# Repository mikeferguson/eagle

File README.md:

## Eagle CAD Stuff

This is a collection of libraries and board designs using Eagle CAD.

## Installing Eagle 7.1 (on Ubuntu 18.04)

    sudo apt-get install gcc-multilib
    sudo apt-get install libxrender1:i386 libxrandr2:i386 libxcursor1:i386 libfreetype6:i386 libfontconfig1:i386 libxi6:i386 libstdc++6:i386 libjpeg62:i386 libssl1.0.0:i386

    wget http://web.cadsoft.de/ftp/eagle/program/7.1/eagle-lin-7.1.0.run
    chmod a+x eagle-lin-7.1.0.run
    ./eagle-lin-7.1.0.run /opt

## Adding Launcher on Ubuntu 18.04
Add a file called eagle.desktop to ~/.local/share/applications:

    #!/usr/bin/env xdg-open
    [Desktop Entry]
    Comment[en_US]=Eagle 7.1
    Terminal=false
    Name[en_US]=Eagle
    Exec=/opt/eagle-7.1.0/bin/eagle
    Type=Application
    Icon=/opt/eagle-7.1.0/bin/eagleicon50.png
    StartupWMClass=dont_care

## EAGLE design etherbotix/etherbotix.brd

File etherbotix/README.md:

# Etherbotix

## Notes

Notes from stuffing Rev. A:
 * DC-DC regulator is too close to Dynamixel headers (has to be installed slightly angled away)
 * X2 footprint is missing direction indicator.
 * X2 footprint should be a bit wider for hand-stuffing.
 * C39, C40 are 22pF (might still be too high)
 * Encoder capacitor values may not be right (too aggressive of a filter)

Need to source 7/16" or 11mm length, 4-40 or M3 standoff (possibly 952-1520-ND)

## Revision History

 * Rev. B - (Forthcoming)
   * Increase size of P1 indicator on X2.
   * Moved ethernet parts away from MD-03 mounting hole
   * TODO: move U3 away from AX headers
   * TODO: move J1 (ethernet jack) up a bit to avoid collision with IMU
   * TODO: update values of C39, C40
   * TODO: update values of C4, C13, C17, C18
   * TODO: move R19, R24, R25 out from under IMU
   * Move M1 encoder filter away from MD-03 mounting hole
   * Add testpads for PE0, PE1, PE4, PA8
   * Add testpads to encoders, clocks, and current sense
   * Add jumper to force bootloader
   * TODO: change away from clikmate connector
 * Rev. A - September 7, 2014
   * First release

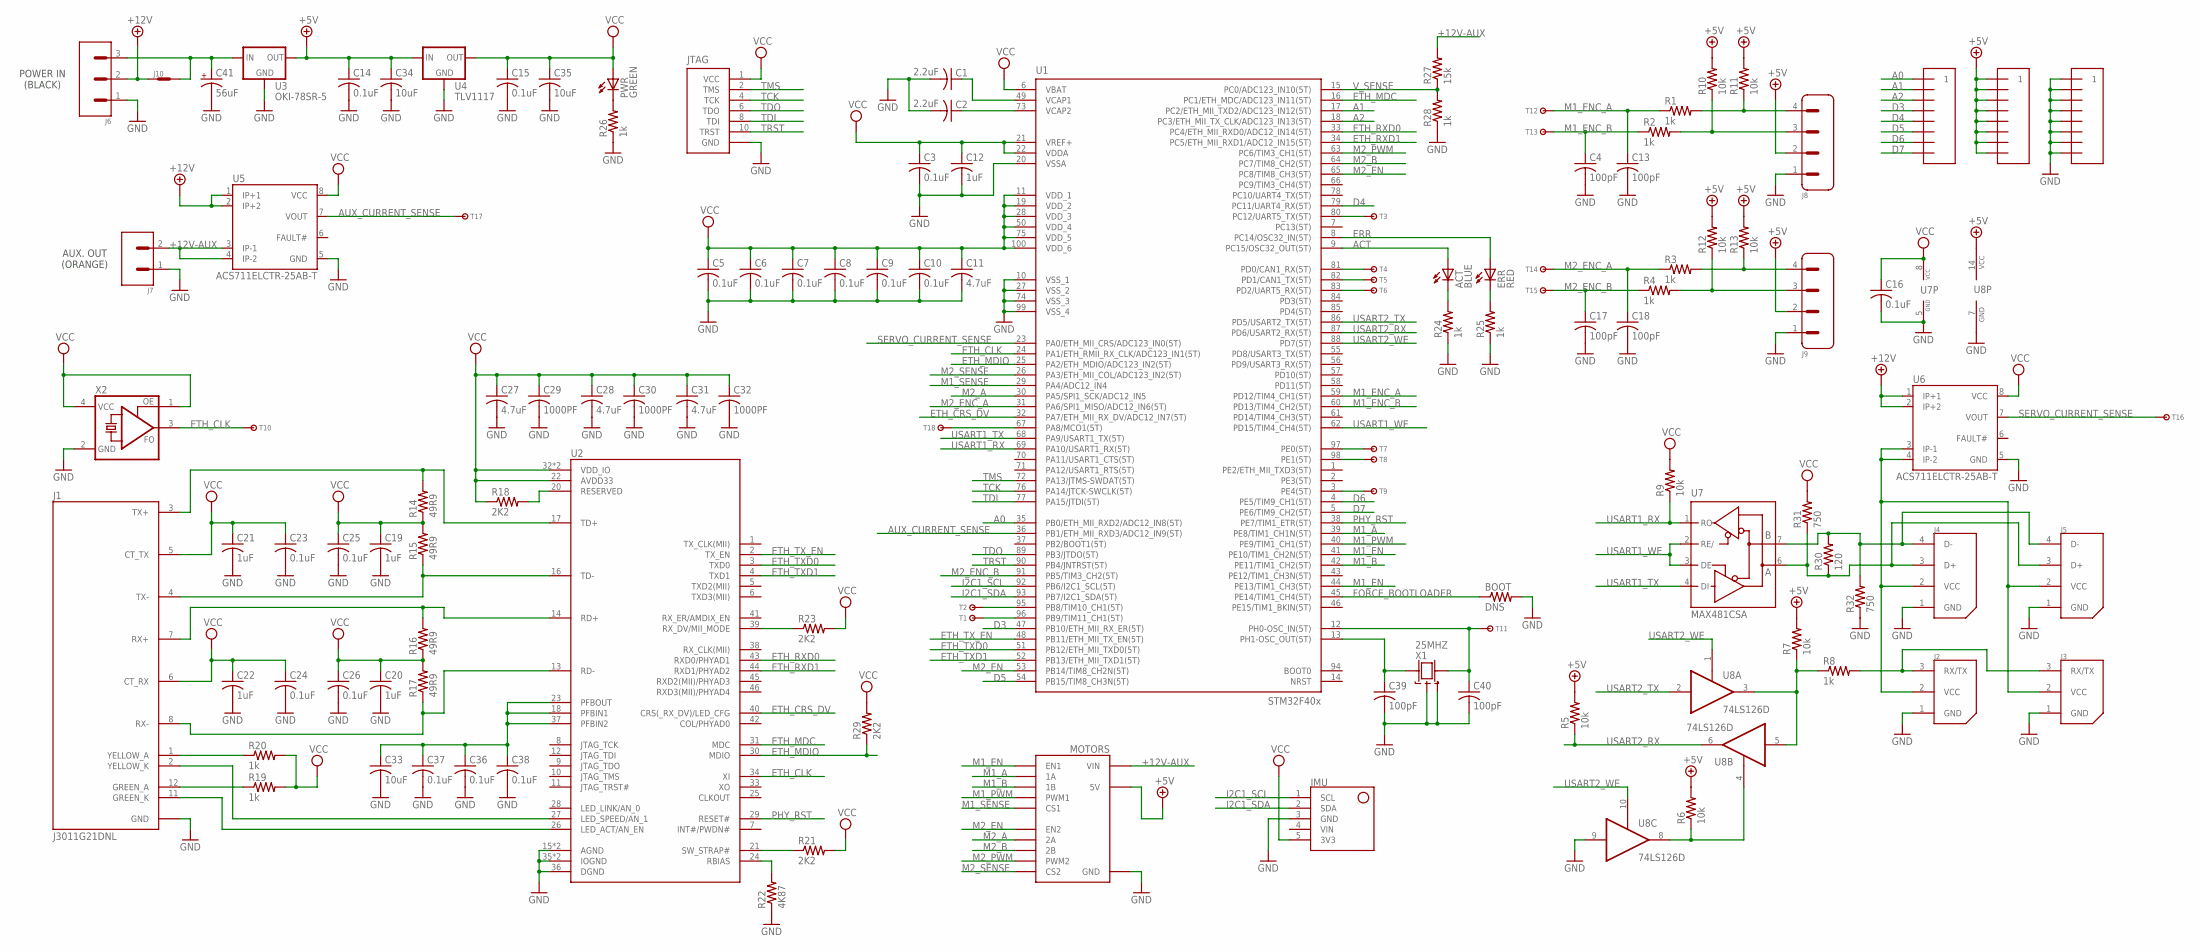
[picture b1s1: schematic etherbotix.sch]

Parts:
ACT: BLUE; LED0603
BOOT: DNS; 0603
C1, C2: 2.2uF; C0603
C3, C5, C6, C7, C8, C9, C10, C14, C15, C16, C23, C24, C25, C26, C36, C37, C38: 0.1uF; C0603
C4, C13, C17, C18, C39, C40: 100pF; C0603
C11, C27, C28, C31: 4.7uF; 0603
C12, C19, C20, C21, C22: 1uF; C0603
C29, C30, C32: 1000PF; 0603
C33, C34, C35: 10uF; C0603
C41: 56uF; OSCON_SVPF_6.3MM
ERR: RED; LED0603
IMU: MINI9IMU
J1: J3011G21DNL; J3
J2, J3: 22-03-5035; 5267-3
J4, J5: 22-03-5045; 5267-4
J6: 1760520000
J7: 1760490000
J8, J9: 502443-0470
J10: JUMPER; J2
JTAG: CORTEX_DEBUG-SHROUDED; 3220-10-0300-00
MOTORS: MD03A
PWR: GREEN; LED0603
R1, R2, R3, R4, R8, R19, R20, R24, R25, R26, R28: 1k; 0603
R5, R6, R7, R9, R10, R11, R12, R13: 10k; 0603
R14, R15, R16, R17: 49R9; 0603
R18, R21, R23, R29: 2K2; 0603
R22: 4K87; 0603
R27: 15k; 0603
R30: 120; 0603
R31, R32: 750; 0603
T1, T2, T3, T4, T5, T6, T7, T8, T9, T10, T11, T12, T13, T14, T15, T16, T17, T18: TESTPAD; TEST
U1: STM32F407V; TQFP100
U2: TLK110; LQFP48
U3: OKI-78SR-5; OKI-78SR
U4: TLV1117; DPAK
U5, U6: ACS711ELCTR-25AB-T; SOIC8
U7: MAX481CSA; SO08
U8: 74LS126D; SO14
U$1, U$2, U$3: HEADER8; 1X8
X1: 25MHZ; 4LCC
X2: ASEMB-50.000MHZ-XY-T; OSCILLATOR

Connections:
+5V: C14.1, C34.1, J8.2, J9.2, MOTORS.5V, R5.2, R6.2, R7.2, R10.2, R11.2, R12.2, R13.2, U3.P$3 (OUT), U4.3 (IN), U8.14 (VCC), U$2.P$1 (1), U$2.P$2, U$2.P$3, U$2.P$4, U$2.P$5, U$2.P$6, U$2.P$7, U$2.P$8
+12V: J6.2, J10.A, U5.1 (IP+1), U5.2 (IP+2), U6.1 (IP+1), U6.2 (IP+2)
+12V-AUX: J7.2, MOTORS.VIN1 (VIN), MOTORS.VIN2 (VIN), R27.2, U5.3 (IP-1), U5.4 (IP-2)
A0: U1.35 (PB0/ETH_MII_RXD2/ADC12_IN8(5T)), U$1.P$1 (1)
A1: U1.17 (PC2/ETH_MII_TXD2/ADC123_IN12(5T)), U$1.P$2
A2: U1.18 (PC3/ETH_MII_TX_CLK/ADC123_IN13(5T)), U$1.P$3
ACT: ACT.A, U1.9 (PC15/OSC32_OUT(5T))
AUX_CURRENT_SENSE: T17.T, U1.36 (PB1/ETH_MII_RXD3/ADC12_IN9(5T)), U5.7 (VOUT)
D3: U1.47 (PB10/ETH_MII_RX_ER(5T)), U$1.P$4
D4: U1.79 (PC11/UART4_RX(5T)), U$1.P$5
D5: U1.54 (PB15/TIM8_CH3N(5T)), U$1.P$6
D6: U1.4 (PE5/TIM9_CH1(5T)), U$1.P$7
D7: U1.5 (PE6/TIM9_CH2(5T)), U$1.P$8
ERR: ERR.A, U1.8 (PC14/OSC32_IN(5T))
ETH_CLK: T10.T, U1.24 (PA1/ETH_RMII_RX_CLK/ADC123_IN1(5T)), U2.34 (XI), X2.3 (FO)
ETH_CRS_DV: U1.32 (PA7/ETH_MII_RX_DV/ADC12_IN7(5T)), U2.40 (CRS(_RX_DV)/LED_CFG)
ETH_MDC: U1.16 (PC1/ETH_MDC/ADC123_IN11(5T)), U2.31 (MDC)
ETH_MDIO: R29.1, U1.25 (PA2/ETH_MDIO/ADC123_IN2(5T)), U2.30 (MDIO)
ETH_RXD0: U1.33 (PC4/ETH_MII_RXD0/ADC12_IN14(5T)), U2.43 (RXD0/PHYAD1)
ETH_RXD1: U1.34 (PC5/ETH_MII_RXD1/ADC12_IN15(5T)), U2.44 (RXD1/PHYAD2)
ETH_TXD0: U1.51 (PB12/ETH_MII_TXD0(5T)), U2.3 (TXD0)
ETH_TXD1: U1.52 (PB13/ETH_MII_TXD1(5T)), U2.4 (TXD1)
ETH_TX_EN: U1.48 (PB11/ETH_MII_TX_EN(5T)), U2.2 (TX_EN)
FORCE_BOOTLOADER: BOOT.1, U1.45 (PE14/TIM1_CH4(5T))
GND: BOOT.2, C1.2, C2.2, C3.2, C4.2, C5.2, C6.2, C7.2, C8.2, C9.2, C10.2, C11.2, C12.2, C13.2, C14.2, C15.2, C16.2, C17.2, C18.2, C19.2, C20.2, C21.2, C22.2, C23.2, C24.2, C25.2, C26.2, C27.2, C28.2, C29.2, C30.2, C31.2, C32.2, C33.2, C34.2, C35.2, C36.2, C37.2, C38.2, C39.2, C40.2, C41.-, IMU.3 (GND), J1.9 (GND), J1.10 (GND), J1.A (GND), J1.B (GND), J2.1 (GND), J3.1 (GND), J4.1 (GND), J5.1 (GND), J6.1, J7.1, J8.1, J9.1, JTAG.3 (GND), JTAG.5 (GND), JTAG.9 (GND), MOTORS.GND1 (GND), MOTORS.GND2 (GND), R22.1, R24.1, R25.1, R26.1, R28.1, R32.1, U1.10 (VSS_1), U1.20 (VSSA), U1.27 (VSS_2), U1.74 (VSS_3), U1.99 (VSS_4), U2.15 (AGND), U2.19 (AGND), U2.35 (IOGND), U2.36 (DGND), U2.47 (IOGND), U3.P$2 (GND), U4.1 (GND), U5.5 (GND), U6.5 (GND), U7.5 (GND), U8.7 (GND), U8.9 (I), U$3.P$1 (1), U$3.P$2, U$3.P$3, U$3.P$4, U$3.P$5, U$3.P$6, U$3.P$7, U$3.P$8, X1.2 (G1), X1.4 (G2), X2.2 (GND)
I2C1_SCL: IMU.1 (SCL), U1.92 (PB6/I2C1_SCL(5T))
I2C1_SDA: IMU.2 (SDA), U1.93 (PB7/I2C1_SDA(5T))
M1_A: MOTORS.1A, U1.39 (PE8/TIM1_CH1N(5T))
M1_B: MOTORS.1B, U1.42 (PE11/TIM1_CH2(5T))
M1_EN: MOTORS.EN1, U1.41 (PE10/TIM1_CH2N(5T)), U1.44 (PE13/TIM1_CH3(5T))
M1_ENC_A: C13.1, R1.1, T12.T, U1.59 (PD12/TIM4_CH1(5T))
M1_ENC_B: C4.1, R2.1, T13.T, U1.60 (PD13/TIM4_CH2(5T))
M1_PWM: MOTORS.PWM1, U1.40 (PE9/TIM1_CH1(5T))
M1_SENSE: MOTORS.CS1, U1.29 (PA4/ADC12_IN4)
M2_A: MOTORS.2A, U1.30 (PA5/SPI1_SCK/ADC12_IN5)
M2_B: MOTORS.2B, U1.64 (PC7/TIM8_CH2(5T))
M2_EN: MOTORS.EN2, U1.53 (PB14/TIM8_CH2N(5T)), U1.65 (PC8/TIM8_CH3(5T))
M2_ENC_A: C18.1, R3.1, T14.T, U1.31 (PA6/SPI1_MISO/ADC12_IN6(5T))
M2_ENC_B: C17.1, R4.1, T15.T, U1.91 (PB5/TIM3_CH2(5T))
M2_PWM: MOTORS.PWM2, U1.63 (PC6/TIM3_CH1(5T))
M2_SENSE: MOTORS.CS2, U1.26 (PA3/ETH_MII_COL/ADC123_IN2(5T))
unnamed: J1.4 (TX-), R15.1, U2.16 (TD-)
unnamed: J2.2 (VCC), J3.2 (VCC), J4.2 (VCC), J5.2 (VCC), U6.3 (IP-1), U6.4 (IP-2)
unnamed: C39.1, U1.13 (PH1-OSC_OUT(5T)), X1.1
unnamed: C1.1, U1.49 (VCAP1)
unnamed: C2.1, U1.73 (VCAP2)
unnamed: J8.3, R2.2, R10.1
unnamed: J8.4, R1.2, R11.1
unnamed: J9.4, R3.2, R13.1
unnamed: J9.3, R4.2, R12.1
unnamed: J4.3 (D+), J5.3 (D+), R30.1, R31.1, U7.6 (A)
unnamed: J4.4 (D-), J5.4 (D-), R30.2, R32.2, U7.7 (B)
unnamed: R7.1, R8.1, U8.3 (O), U8.5 (I)
unnamed: R6.1, U8.4 (OE), U8.8 (O)
unnamed: J2.3 (RX/TX), J3.3 (RX/TX), R8.2
unnamed: C40.1, T11.T, U1.12 (PH0-OSC_IN(5T)), X1.3
unnamed: J1.3 (TX+), R14.2, U2.17 (TD+)
unnamed: R18.2, U2.20 (RESERVED)
unnamed: J1.2 (YELLOW_K), U2.27 (LED_SPEED/AN_1)
unnamed: J1.7 (RX+), R16.2, U2.14 (RD+)
unnamed: J1.11 (GREEN_K), U2.26 (LED_ACT/AN_EN)
unnamed: J1.8 (RX-), R17.1, U2.13 (RD-)
unnamed: J1.1 (YELLOW_A), R20.1
unnamed: J1.12 (GREEN_A), R19.1
unnamed: C33.1, C36.1, C37.1, C38.1, U2.18 (PFBIN1), U2.23 (PFBOUT), U2.37 (PFBIN2)
unnamed: R21.1, U2.21 (SW_STRAP#)
unnamed: R22.2, U2.24 (RBIAS)
unnamed: R23.1, U2.39 (RX_DV/MII_MODE)
unnamed: PWR.C, R26.2
unnamed: C41.+, J6.3, J10.B, U3.P$1 (IN)
unnamed: ERR.C, R25.2
unnamed: ACT.C, R24.2
PA8: T18.T, U1.67 (PA8/MCO1(5T))
PB8: T2.T, U1.95 (PB8/TIM10_CH1(5T))
PB9: T1.T, U1.96 (PB9/TIM11_CH1(5T))
PC12: T3.T, U1.80 (PC12/UART5_TX(5T))
PD0: T4.T, U1.81 (PD0/CAN1_RX(5T))
PD1: T5.T, U1.82 (PD1/CAN1_TX(5T))
PD2: T6.T, U1.83 (PD2/UART5_RX(5T))
PE0: T7.T, U1.97 (PE0(5T))
PE1: T8.T, U1.98 (PE1(5T))
PE4: T9.T, U1.3 (PE4(5T))
PHY_RST: U1.38 (PE7/TIM1_ETR(5T)), U2.29 (RESET#)
SERVO_CURRENT_SENSE: T16.T, U1.23 (PA0/ETH_MII_CRS/ADC123_IN0(5T)), U6.7 (VOUT)
TCK: JTAG.4 (TCK), U1.76 (PA14/JTCK-SWCLK(5T))
TDI: JTAG.8 (TDI), U1.77 (PA15/JTDI(5T))
TDO: JTAG.6 (TDO), U1.89 (PB3/JTDO(5T))
TMS: JTAG.2 (TMS), U1.72 (PA13/JTMS-SWDAT(5T))
TRST: JTAG.10 (TRST), U1.90 (PB4/JNTRST(5T))
USART1_RX: R9.1, U1.69 (PA10/USART1_RX(5T)), U7.1 (RO)
USART1_TX: U1.68 (PA9/USART1_TX(5T)), U7.4 (DI)
USART1_WE: U1.62 (PD15/TIM4_CH4(5T)), U7.2 (RE/), U7.3 (DE)
USART2_RX: R5.1, U1.87 (PD6/USART2_RX(5T)), U8.6 (O)
USART2_TX: U1.86 (PD5/USART2_TX(5T)), U8.2 (I)
USART2_WE: U1.88 (PD7(5T)), U8.1 (OE), U8.10 (OE)
VCC: C3.1, C5.1, C6.1, C7.1, C8.1, C9.1, C10.1, C11.1, C12.1, C15.1, C16.1, C19.1, C20.1, C21.1, C22.1, C23.1, C24.1, C25.1, C26.1, C27.1, C28.1, C29.1, C30.1, C31.1, C32.1, C35.1, IMU.5 (3V3), J1.5 (CT_TX), J1.6 (CT_RX), JTAG.1 (VCC), PWR.A, R9.2, R14.1, R15.2, R16.1, R17.2, R18.1, R19.2, R20.2, R21.2, R23.2, R29.2, R31.2, U1.6 (VBAT), U1.11 (VDD_1), U1.19 (VDD_2), U1.21 (VREF+), U1.22 (VDDA), U1.28 (VDD_3), U1.50 (VDD_4), U1.75 (VDD_5), U1.100 (VDD_6), U2.22 (AVDD33), U2.32 (VDD_IO), U2.48 (VDD_IO), U4.4 (OUT), U5.8 (VCC), U6.8 (VCC), U7.8 (VCC), X2.1 (OE), X2.4 (VCC)
V_SENSE: R27.1, R28.2, U1.15 (PC0/ADC123_IN10(5T))

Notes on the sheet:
POWER IN (BLACK)
AUX. OUT (ORANGE)

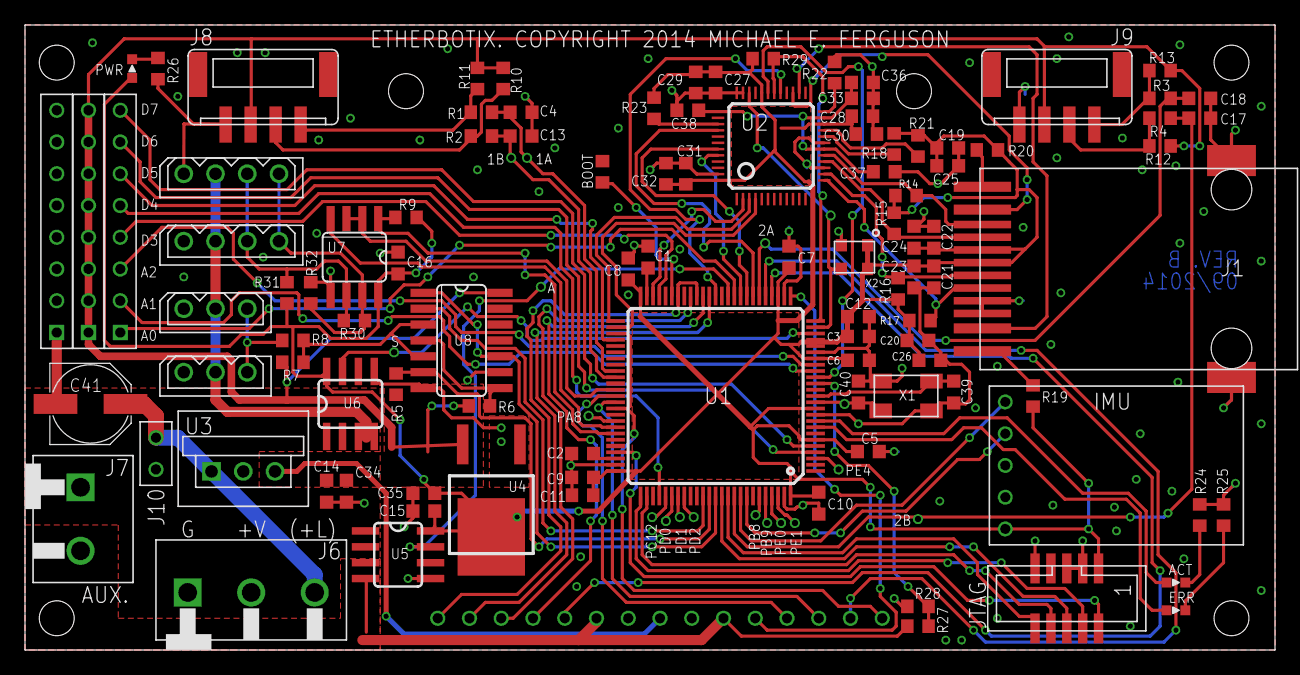
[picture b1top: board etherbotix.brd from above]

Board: 2 copper layers, 100.0 x 50.0 mm, 121 parts (0 on the bottom side), 97 nets.

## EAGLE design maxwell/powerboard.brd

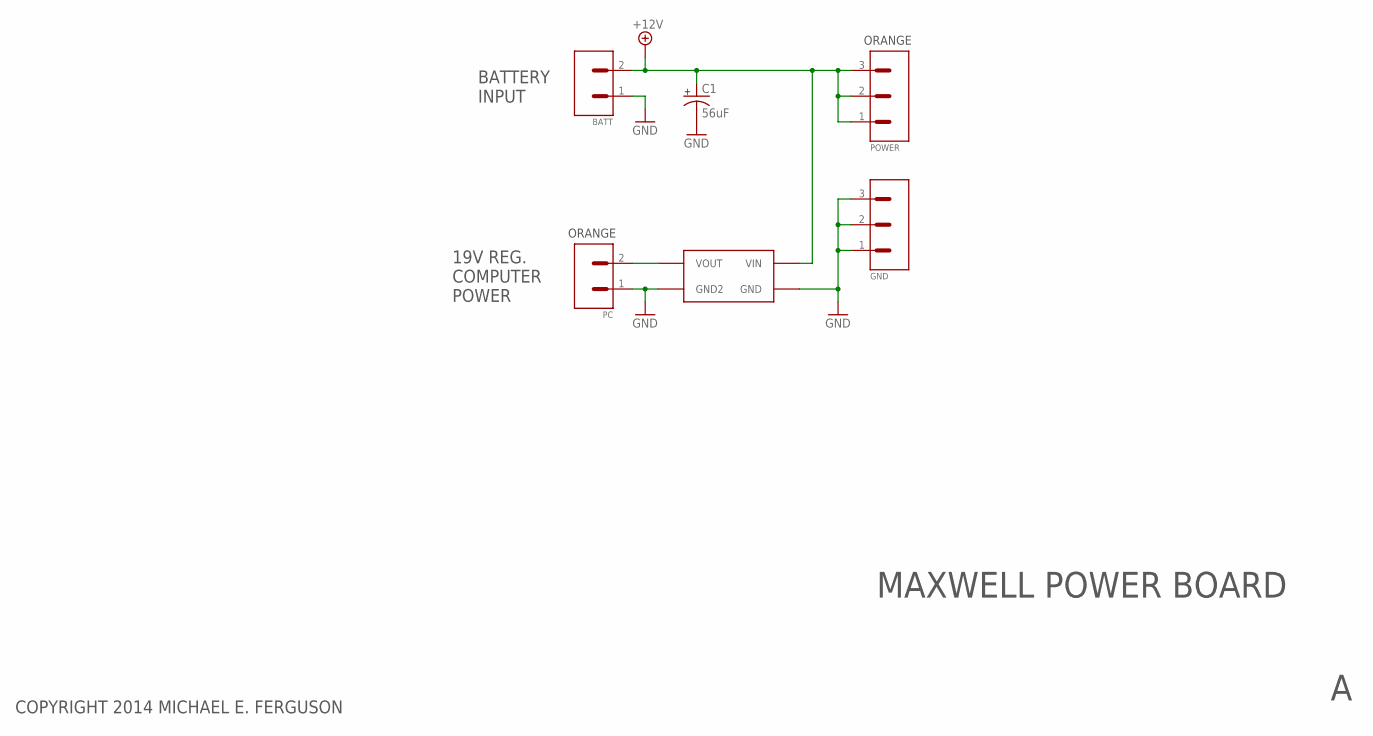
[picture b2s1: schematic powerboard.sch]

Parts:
BATT: 1760510000; 1760490000
C1: 56uF; OSCON_SVPF_6.3MM
GND: 1760520000
PC: 1760490000
POWER: 1760520000
U3V50AVH: U3V50AHV

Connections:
+12V: BATT.2, C1.+, POWER.1, POWER.2, POWER.3, U3V50AVH.V_IN (VIN)
GND: BATT.1, C1.-, GND.1, GND.2, GND.3, PC.1, U3V50AVH.GND_IN (GND), U3V50AVH.GND_OUT (GND2)
unnamed: PC.2, U3V50AVH.V_OUT (VOUT)

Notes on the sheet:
BATTERY INPUT
19V REG. COMPUTER POWER
ORANGE
MAXWELL POWER BOARD
COPYRIGHT 2014 MICHAEL E. FERGUSON

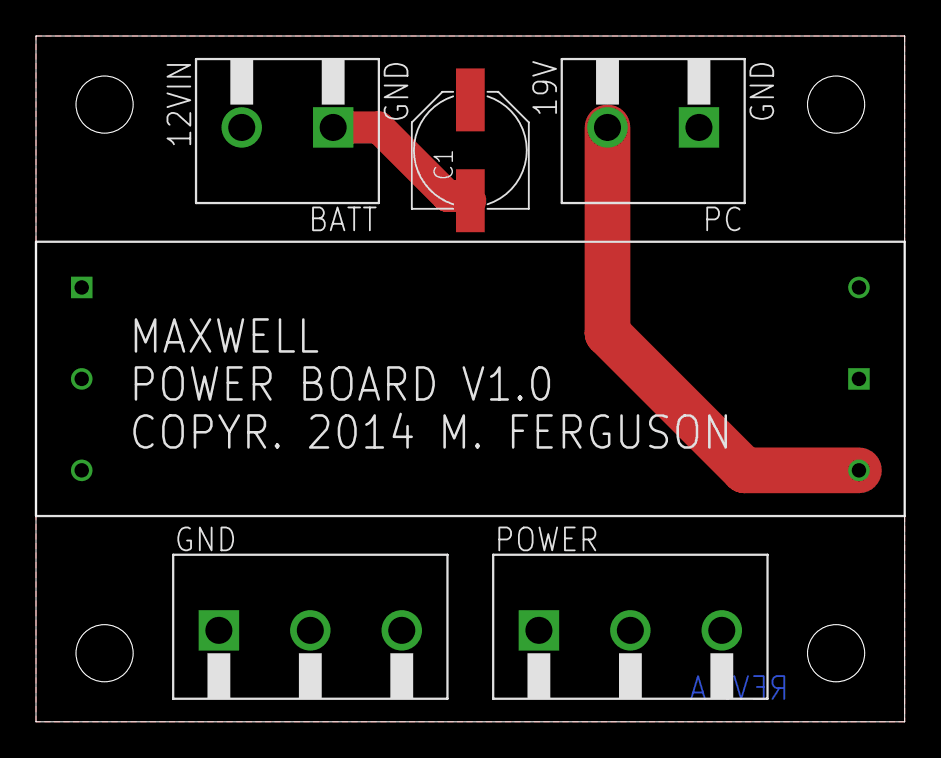
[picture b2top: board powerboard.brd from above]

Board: 2 copper layers, 48.3 x 38.1 mm, 6 parts (0 on the bottom side), 3 nets.

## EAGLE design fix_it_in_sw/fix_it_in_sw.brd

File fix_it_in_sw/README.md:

# Fix-it-in-software
This board was a simple STM32F4 board using the 64-lqfp part. It was
designed for a battle bot that was never built. It includes:

 * 2 medium-current motor drivers
 * 2 encoder inputs
 * Header for Pololu Mini-IMU v2
 * Bidirectional current sense
 * Headers connected to appropriate timers for RC inputs

The software was never really finished.

This design was done in Eagle 5.x and imported to Eagle 7.1 -- it has
not been tested (there may be issues with the import)

This board is sized to work with SeeedStudio's 5cm X 5cm size limit.

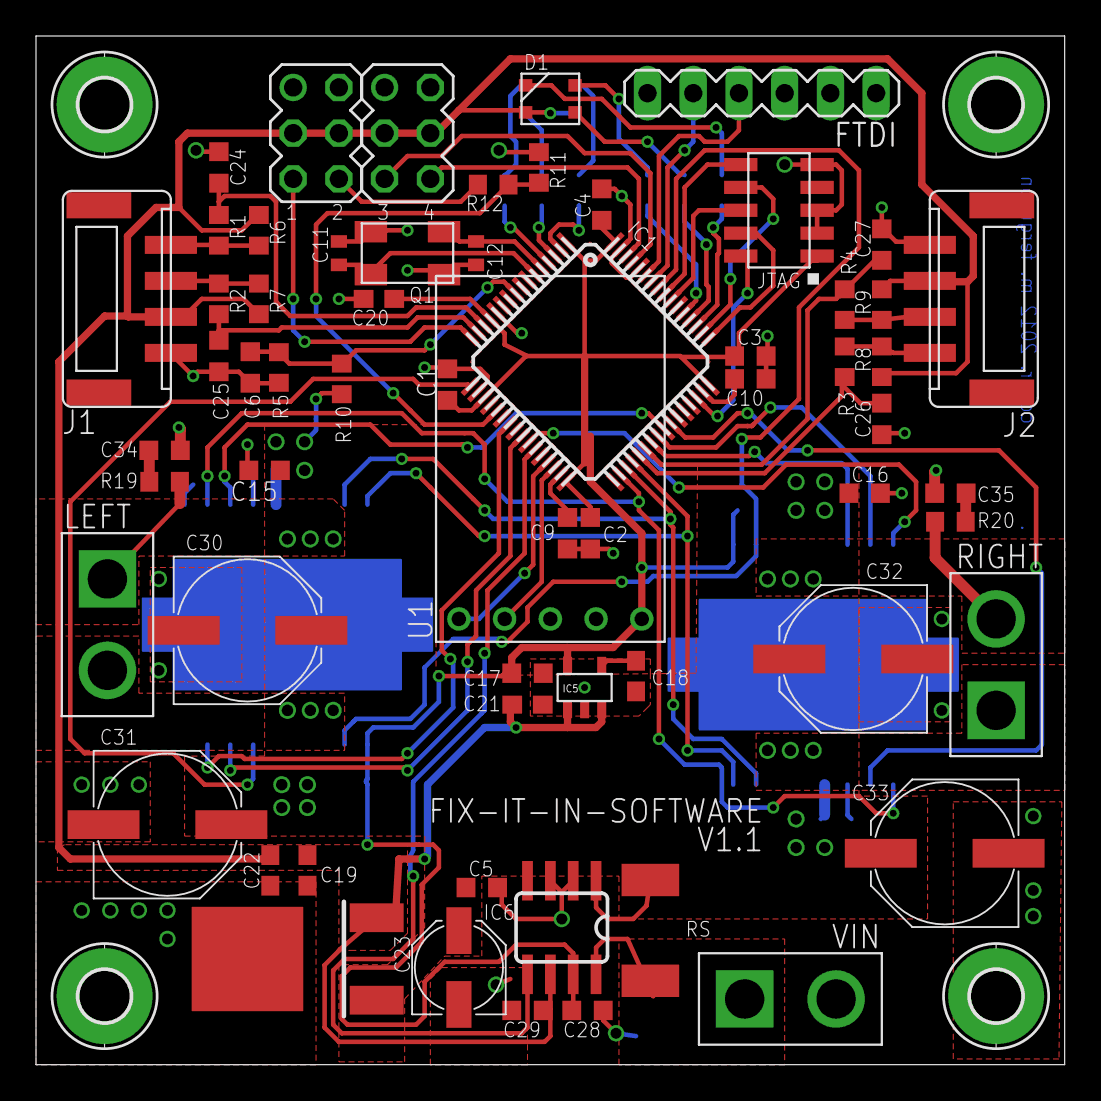
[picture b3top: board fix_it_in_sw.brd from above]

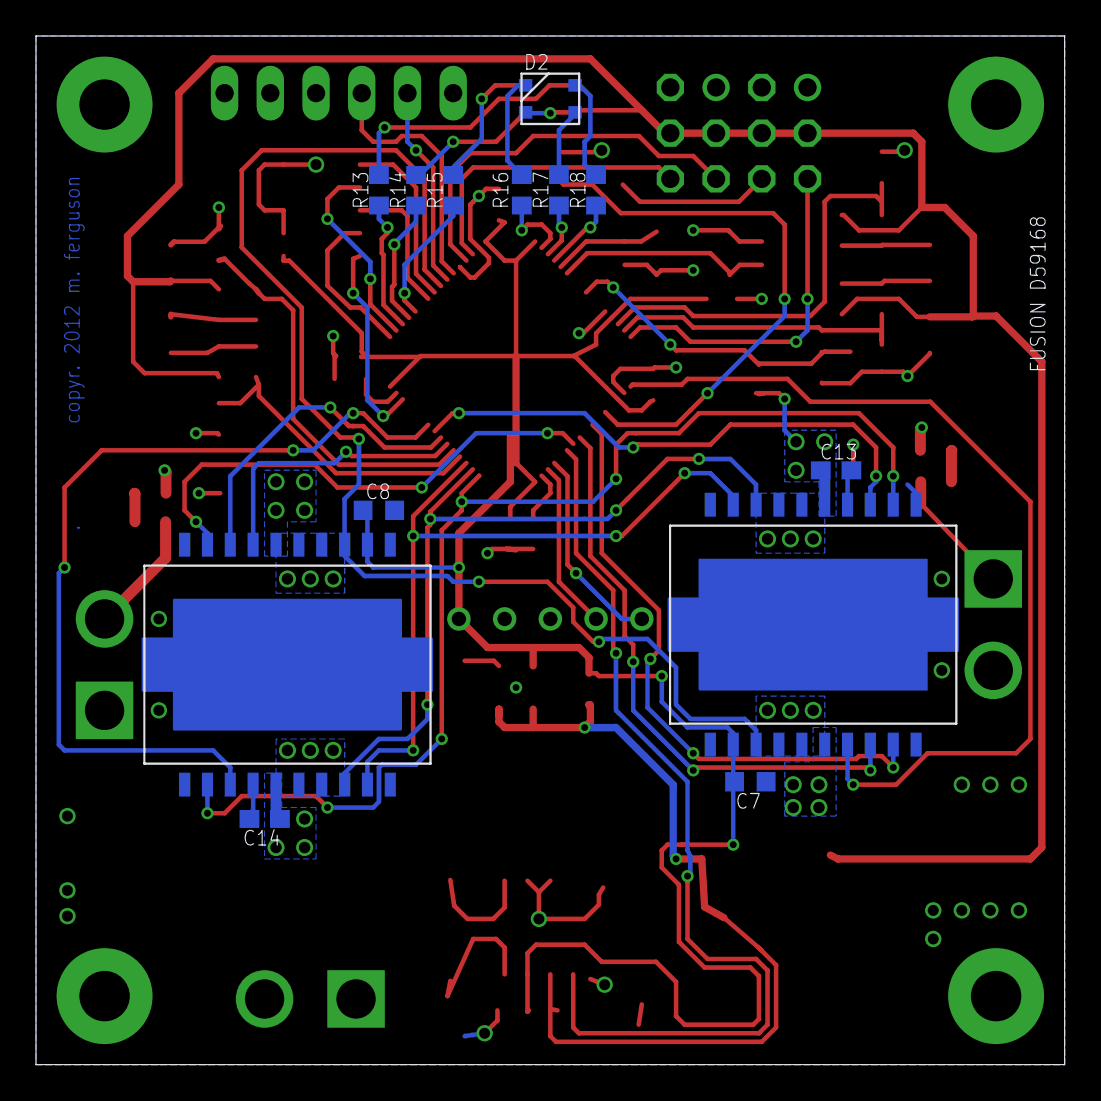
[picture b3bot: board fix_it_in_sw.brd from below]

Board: 2 copper layers, 57.1 x 57.1 mm, 79 parts (13 on the bottom side), 66 nets.

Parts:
C1, C2, C3, C4, C5, C6, C7, C8, C15, C16, C28, C29: 0.1uF; C0603
C9, C10, C17: 2.2uF; C0603
C11, C12: 33pF; C0402
C13, C14: 22000pF; C0603
C18: 470pF; C0603
C19, C20, C21: 1uF; C0603
C22: 10uF; C0603
C23: 33uF; PANASONIC_C
C24, C25, C26, C27: 100pF; C0603
C30, C31, C32, C33: 100uF; PANASONIC_F
C34, C35: C0603
D1, D2: CREE-PLCC-4
FTDI: MA06-1
H1, H2, H3, H4: MOUNT-PAD-ROUND2.8; 2,8-PAD
IC1: STM32F405RG; TQFP64
IC2, IC3: NCV7729BPPR2G; PSOP-20
IC4: NCP5501DT50RKG; DPAK
IC5: TPS79933DDCR; SOT-23-5
IC6: AD8205R; SO8
J1, J2: 502443-0470
JTAG: GRPB052VWQS-RC; DEBUG
LEFT: POWER
Q1: 8MHZ; 4LCC
R1, R2, R3, R4, R5, R13, R14, R15, R16, R17, R18: 1k; R0603
R6, R7, R8, R9, R10, R11: 2k49; R0603
R12: 1k5; R0603
R19, R20: R0603
RIGHT: POWER
RS: R2512
SV1, SV2: MA03-2
U1: MINI9IMU
VIN: POWER

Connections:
+5V: C19.1, C21.1, C22.1, C29.1, D1.2, D2.2, IC4.3, IC5.1, IC5.3, IC6.6, J1.2, J2.2, R6.2, R7.2, R8.2, R9.2, SV1.3, SV1.4, SV2.3, SV2.4
+7V: C5.1, C13.1, C14.1, C15.1, C16.1, C23.+, C30.+, C31.+, C32.+, C33.+, IC2.5, IC2.16, IC3.5, IC3.16, IC4.1, IC6.1, R10.2, RS.2
BOT_B: IC1.4, R18.2
BOT_G: IC1.3, R17.2
BOT_R: IC1.2, R16.2
CH1: IC1.16, SV1.5
CH2: IC1.21, R11.2, R12.1
CH3: IC1.61, SV2.5
CH4: IC1.62, SV2.6
CURRENT_SENSE: IC1.27, IC6.5
GND: C1.2, C2.2, C3.2, C4.2, C5.2, C6.2, C7.2, C8.2, C9.2, C10.2, C11.2, C12.2, C15.2, C16.2, C17.2, C18.2, C19.2, C20.2, C21.2, C22.2, C23.-, C24.2, C25.2, C26.2, C27.2, C28.2, C29.2, C30.-, C31.-, C32.-, C33.-, C34.2, C35.2, FTDI.1, FTDI.2, IC1.12, IC1.18, IC1.60, IC1.63, IC2.1, IC2.10, IC2.11, IC2.20, IC2.THERMAL, IC3.1, IC3.10, IC3.11, IC3.20, IC3.THERMAL, IC4.4, IC5.2, IC6.2, IC6.3, J1.1, J2.1, JTAG.3, JTAG.5, JTAG.9, Q1.2, Q1.4, R5.1, R11.1, SV1.1, SV1.2, SV2.1, SV2.2, U1.3, VIN.-
L+: IC2.6, IC2.7, LEFT.+, R19.2
L-: IC2.14, IC2.15, LEFT.-
LEFT_CS: IC1.17, IC2.17
LEFT_ENC_A: C24.1, IC1.14, R1.2
LEFT_ENC_B: C25.1, IC1.15, R2.2
L_FAULT: IC1.25, IC2.18
MISO: IC1.35, IC2.8, IC3.8
MOSI: IC1.36, IC2.9, IC3.9
M_EN: IC1.57, IC2.13, IC3.13
unnamed: R12.2, SV1.6
unnamed: C11.1, IC1.6, Q1.1
unnamed: J1.4, R1.1, R6.1
unnamed: C12.1, IC1.5, Q1.3
unnamed: J1.3, R2.1, R7.1
unnamed: C9.1, IC1.31
unnamed: C34.1, R19.1
unnamed: C35.1, R20.1
unnamed: C13.2, IC2.4
unnamed: J2.4, R3.1, R8.1
unnamed: C10.1, IC1.47
unnamed: C14.2, IC3.4
unnamed: C18.1, IC5.4
unnamed: D2.4, R18.1
unnamed: J2.3, R4.1, R9.1
unnamed: D2.3, R17.1
unnamed: D2.1, R16.1
unnamed: D1.1, R13.1
unnamed: D1.3, R14.1
unnamed: D1.4, R15.1
R+: IC3.6, IC3.7, RIGHT.+
R-: IC3.14, IC3.15, R20.2, RIGHT.-
RIGHT_CS: IC1.39, IC3.17
RIGHT_ENC_A: C26.1, IC1.37, R3.2
RIGHT_ENC_B: C27.1, IC1.38, R4.2
RX: FTDI.4, IC1.59
R_FAULT: IC1.40, IC3.18
SCK: IC1.34, IC2.2, IC3.2
SCL: IC1.29, U1.1
SDA: IC1.30, U1.2
TCK: IC1.49, JTAG.4
TDI: IC1.50, JTAG.8
TDO: IC1.55, JTAG.6
TIM1_CH1: IC1.41, IC2.3
TIM1_CH1N: IC1.23, IC2.19
TIM1_CH2: IC1.42, IC3.3
TIM1_CH2N: IC1.26, IC3.19
TMS: IC1.46, JTAG.2
TOP_B: IC1.53, R15.2
TOP_G: IC1.52, R14.2
TOP_R: IC1.51, R13.2
TRST: IC1.56, JTAG.10
TX: FTDI.5, IC1.58
VCC: C1.1, C2.1, C3.1, C4.1, C7.1, C8.1, C17.1, C20.1, C28.1, IC1.1, IC1.13, IC1.19, IC1.32, IC1.48, IC1.64, IC2.12, IC3.12, IC5.5, IC6.7, JTAG.1, U1.5
VIN: IC6.8, RS.1, VIN.+
VOLTAGE_SENSE: C6.1, IC1.9, R5.2, R10.1

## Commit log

2014-09-03 add README
2014-09-03 add fix_it_in_sw
2014-09-03 import ftdi from private repo
2014-09-03 add headers library
2014-09-03 add gitignore for eagle backup files
2014-09-03 add stm library from stm32 repo
2014-09-03 import pololu library with IMU
2014-09-03 add ethernet parts, including new TI TLK110
2014-09-03 add description to headers
2014-09-03 add molex library
2014-09-03 add MD03A to pololu library
2014-09-03 add power library
2014-09-03 add library of standard components
2014-09-03 check in start of new etherbotix board
2014-09-04 add 50mhz oscillator
2014-09-05 remove extra silkscreen from MD03
2014-09-05 routed, still needs cleanup
2014-09-05 add some more resistors/caps
2014-09-05 adjust ethernet parts for easier schematic routing
2014-09-05 pass DRC
2014-09-05 fix part number of 1760510000
2014-09-05 add small testpad
2014-09-05 add testpads
2014-09-05 add notes to silkscreen
2014-09-05 minor tweaks to silkscreen
2014-09-05 check in gerber generation config for seeed
2014-09-06 fix sizing of MD03
2014-09-06 move imu slightly down
2014-09-06 add DRU from seeed
2014-09-06 some more refinements
2014-09-07 add 3P terminal block, black
2014-09-07 add estop-capable 3-pin VIN header
2014-09-07 add top-side ground plane
2014-09-07 switch MD03A outline to tDocu
2014-09-07 update footprint of TLV1117
2014-09-07 nearly done with layout
2014-09-07 final rev. A updates
2014-09-07 upload gerber package for rev. A
2014-09-20 add notes from stuffing first etherbotix
2014-09-20 allegro library was not under revision control
2014-09-20 add notes on MD03 standoff
2014-09-22 start rev. B
2014-09-22 add testpads to clocks, encoders, current sense
2014-09-22 add testpad for PA8 (mco1)
2014-10-11 add new powerboard for maxwell
2014-10-15 add pololu motor driver and step up regulator
2014-10-15 add maxwell schematic, some schematic elements
2014-10-19 add pin to force staying in bootloader
2015-02-12 Adding board mount files. Including two configurations.
2015-02-12 Adding filets to screw holes.
2015-06-20 increase size of pin 1 indicator on X2
2015-06-20 move parts away from MD-03 hole
2018-04-03 reorganize so both revisions of etherbotix are visible
2018-04-03 update tested status on parts used in etherbotix
2018-04-05 fix motor wires that were reversed
2018-04-12 add a1335
2018-04-13 add 6P clikmate
2018-04-13 add DRV8332
2018-04-14 add RTE24005
2018-04-24 reorder pins, cleans up schematic
2018-04-24 add 3,4,8P vertical microfit
2018-04-24 add FPC, smaller clik-mate connectors
2018-04-24 add CUI power regulators
2018-04-24 add current sense resistor
2018-04-25 add AD8418
2018-04-25 add drv8313
2018-04-26 add some parts
2018-05-01 update qfp64 package, move pin drawing to tdoc layer
2018-05-01 fix name of a1335 part
2018-05-01 add and update some parts
2018-05-09 add warning about DPak versions
2018-05-09 add parts
2018-05-11 add 8P 24A pheonix term block
2018-05-15 add parts, fix pin order of VC78-1000
2018-05-18 add vx7805-500
2018-05-24 minor part updates
2018-05-28 update readme with 18.04 instructions
2018-08-28 fix orientation of FFC for maxon motors
2018-09-03 add a number of molex connectors
2020-04-23 add PDF of schematic

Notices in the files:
etherbotix/etherbotix.brd:
ETHERBOTIX. COPYRIGHT 2014 MICHAEL E. FERGUSON
